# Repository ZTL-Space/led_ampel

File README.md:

# led_ampel
LED-Circui-Board for an old swiss train signal

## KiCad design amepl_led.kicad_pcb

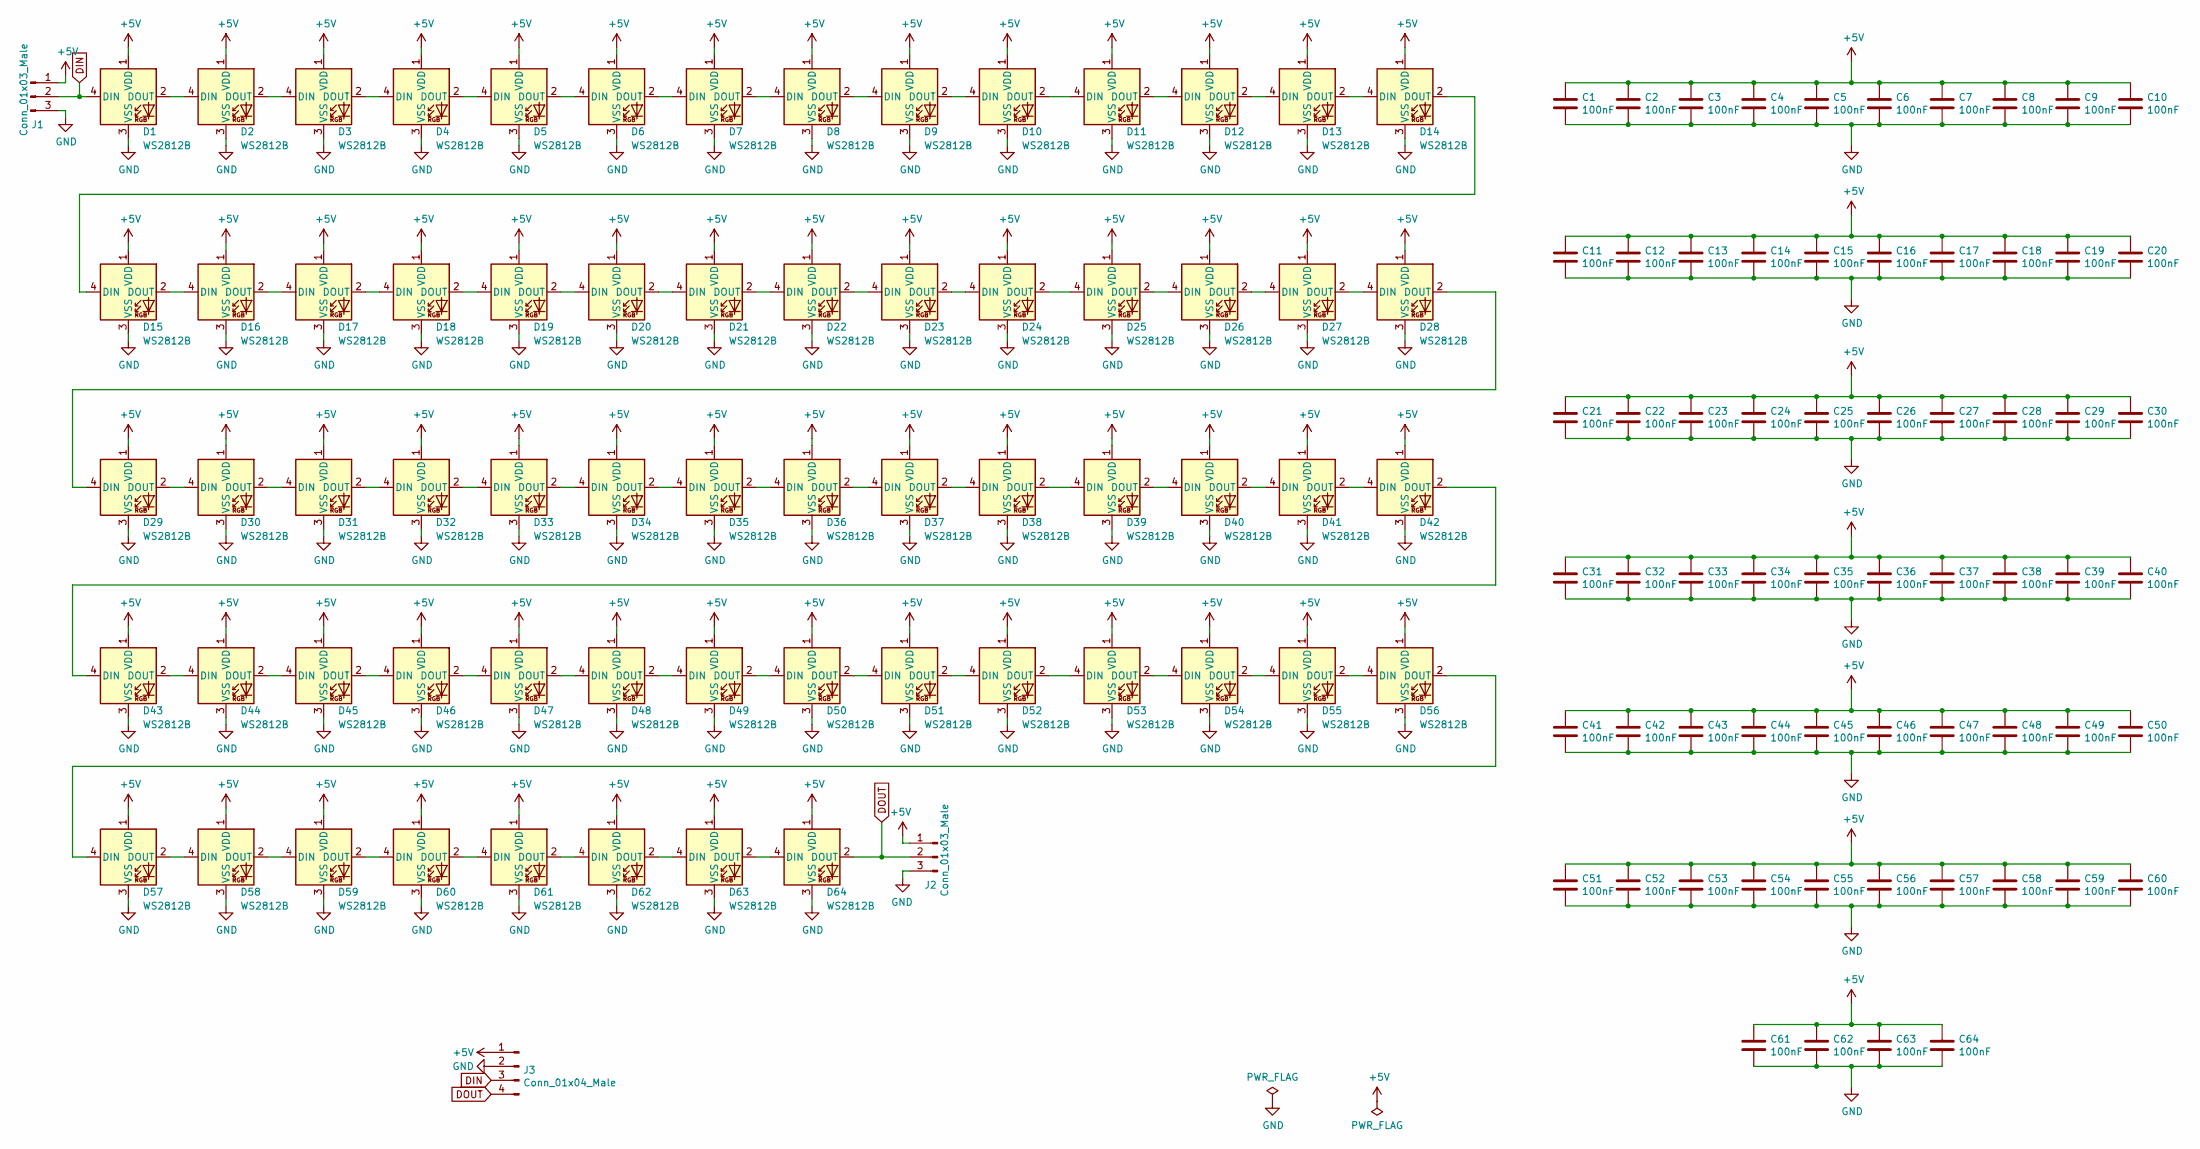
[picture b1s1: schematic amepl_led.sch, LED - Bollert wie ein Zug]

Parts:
C1, C2, C3, C4, C5, C6, C7, C8, C9, C10, C11, C12, C13, C14, C15, C16, C17, C18, C19, C20, C21, C22, C23, C24, C25, C26, C27, C28, C29, C30, C31, C32, C33, C34, C35, C36, C37, C38, C39, C40, C41, C42, C43, C44, C45, C46, C47, C48, C49, C50, C51, C52, C53, C54, C55, C56, C57, C58, C59, C60, C61, C62, C63, C64: 100nF; C_0805_2012Metric_Pad1.18x1.45mm_HandSolder
D1, D2, D3, D4, D5, D6, D7, D8, D9, D10, D11, D12, D13, D14, D15, D16, D17, D18, D19, D20, D21, D22, D23, D24, D25, D26, D27, D28, D29, D30, D31, D32, D33, D34, D35, D36, D37, D38, D39, D40, D41, D42, D43, D44, D45, D46, D47, D48, D49, D50, D51, D52, D53, D54, D55, D56, D57, D58, D59, D60, D61, D62, D63, D64: WS2812B; LED_WS2812B_PLCC4_5.0x5.0mm_P3.2mm
J1, J2: Conn_01x03_Male; JST_XH_B3B-XH-A_1x03_P2.50mm_Vertical
J3: Conn_01x04_Male; PinHeader_1x04_P2.54mm_Vertical

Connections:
+5V: C1.1, C2.1, C3.1, C4.1, C5.1, C6.1, C7.1, C8.1, C9.1, C10.1, C11.1, C12.1, C13.1, C14.1, C15.1, C16.1, C17.1, C18.1, C19.1, C20.1, C21.1, C22.1, C23.1, C24.1, C25.1, C26.1, C27.1, C28.1, C29.1, C30.1, C31.1, C32.1, C33.1, C34.1, C35.1, C36.1, C37.1, C38.1, C39.1, C40.1, C41.1, C42.1, C43.1, C44.1, C45.1, C46.1, C47.1, C48.1, C49.1, C50.1, C51.1, C52.1, C53.1, C54.1, C55.1, C56.1, C57.1, C58.1, C59.1, C60.1, C61.1, C62.1, C63.1, C64.1, D1.1 (VDD), D2.1 (VDD), D3.1 (VDD), D4.1 (VDD), D5.1 (VDD), D6.1 (VDD), D7.1 (VDD), D8.1 (VDD), D9.1 (VDD), D10.1 (VDD), D11.1 (VDD), D12.1 (VDD), D13.1 (VDD), D14.1 (VDD), D15.1 (VDD), D16.1 (VDD), D17.1 (VDD), D18.1 (VDD), D19.1 (VDD), D20.1 (VDD), D21.1 (VDD), D22.1 (VDD), D23.1 (VDD), D24.1 (VDD), D25.1 (VDD), D26.1 (VDD), D27.1 (VDD), D28.1 (VDD), D29.1 (VDD), D30.1 (VDD), D31.1 (VDD), D32.1 (VDD), D33.1 (VDD), D34.1 (VDD), D35.1 (VDD), D36.1 (VDD), D37.1 (VDD), D38.1 (VDD), D39.1 (VDD), D40.1 (VDD), D41.1 (VDD), D42.1 (VDD), D43.1 (VDD), D44.1 (VDD), D45.1 (VDD), D46.1 (VDD), D47.1 (VDD), D48.1 (VDD), D49.1 (VDD), D50.1 (VDD), D51.1 (VDD), D52.1 (VDD), D53.1 (VDD), D54.1 (VDD), D55.1 (VDD), D56.1 (VDD), D57.1 (VDD), D58.1 (VDD), D59.1 (VDD), D60.1 (VDD), D61.1 (VDD), D62.1 (VDD), D63.1 (VDD), D64.1 (VDD), J1.1, J2.1, J3.1
DIN: D1.4 (DIN), J1.2, J3.3
DOUT: D64.2 (DOUT), J2.2, J3.4
GND: C1.2, C2.2, C3.2, C4.2, C5.2, C6.2, C7.2, C8.2, C9.2, C10.2, C11.2, C12.2, C13.2, C14.2, C15.2, C16.2, C17.2, C18.2, C19.2, C20.2, C21.2, C22.2, C23.2, C24.2, C25.2, C26.2, C27.2, C28.2, C29.2, C30.2, C31.2, C32.2, C33.2, C34.2, C35.2, C36.2, C37.2, C38.2, C39.2, C40.2, C41.2, C42.2, C43.2, C44.2, C45.2, C46.2, C47.2, C48.2, C49.2, C50.2, C51.2, C52.2, C53.2, C54.2, C55.2, C56.2, C57.2, C58.2, C59.2, C60.2, C61.2, C62.2, C63.2, C64.2, D1.3 (VSS), D2.3 (VSS), D3.3 (VSS), D4.3 (VSS), D5.3 (VSS), D6.3 (VSS), D7.3 (VSS), D8.3 (VSS), D9.3 (VSS), D10.3 (VSS), D11.3 (VSS), D12.3 (VSS), D13.3 (VSS), D14.3 (VSS), D15.3 (VSS), D16.3 (VSS), D17.3 (VSS), D18.3 (VSS), D19.3 (VSS), D20.3 (VSS), D21.3 (VSS), D22.3 (VSS), D23.3 (VSS), D24.3 (VSS), D25.3 (VSS), D26.3 (VSS), D27.3 (VSS), D28.3 (VSS), D29.3 (VSS), D30.3 (VSS), D31.3 (VSS), D32.3 (VSS), D33.3 (VSS), D34.3 (VSS), D35.3 (VSS), D36.3 (VSS), D37.3 (VSS), D38.3 (VSS), D39.3 (VSS), D40.3 (VSS), D41.3 (VSS), D42.3 (VSS), D43.3 (VSS), D44.3 (VSS), D45.3 (VSS), D46.3 (VSS), D47.3 (VSS), D48.3 (VSS), D49.3 (VSS), D50.3 (VSS), D51.3 (VSS), D52.3 (VSS), D53.3 (VSS), D54.3 (VSS), D55.3 (VSS), D56.3 (VSS), D57.3 (VSS), D58.3 (VSS), D59.3 (VSS), D60.3 (VSS), D61.3 (VSS), D62.3 (VSS), D63.3 (VSS), D64.3 (VSS), J1.3, J2.3, J3.2
unnamed: D1.2 (DOUT), D2.4 (DIN)
unnamed: D2.2 (DOUT), D3.4 (DIN)
unnamed: D3.2 (DOUT), D4.4 (DIN)
unnamed: D4.2 (DOUT), D5.4 (DIN)
unnamed: D5.2 (DOUT), D6.4 (DIN)
unnamed: D6.2 (DOUT), D7.4 (DIN)
unnamed: D7.2 (DOUT), D8.4 (DIN)
unnamed: D8.2 (DOUT), D9.4 (DIN)
unnamed: D10.2 (DOUT), D11.4 (DIN)
unnamed: D9.2 (DOUT), D10.4 (DIN)
unnamed: D11.2 (DOUT), D12.4 (DIN)
unnamed: D12.2 (DOUT), D13.4 (DIN)
unnamed: D13.2 (DOUT), D14.4 (DIN)
unnamed: D14.2 (DOUT), D15.4 (DIN)
unnamed: D15.2 (DOUT), D16.4 (DIN)
unnamed: D16.2 (DOUT), D17.4 (DIN)
unnamed: D17.2 (DOUT), D18.4 (DIN)
unnamed: D18.2 (DOUT), D19.4 (DIN)
unnamed: D19.2 (DOUT), D20.4 (DIN)
unnamed: D20.2 (DOUT), D21.4 (DIN)
unnamed: D21.2 (DOUT), D22.4 (DIN)
unnamed: D22.2 (DOUT), D23.4 (DIN)
unnamed: D23.2 (DOUT), D24.4 (DIN)
unnamed: D24.2 (DOUT), D25.4 (DIN)
unnamed: D25.2 (DOUT), D26.4 (DIN)
unnamed: D26.2 (DOUT), D27.4 (DIN)
unnamed: D27.2 (DOUT), D28.4 (DIN)
unnamed: D28.2 (DOUT), D29.4 (DIN)
unnamed: D29.2 (DOUT), D30.4 (DIN)
unnamed: D30.2 (DOUT), D31.4 (DIN)
unnamed: D31.2 (DOUT), D32.4 (DIN)
unnamed: D32.2 (DOUT), D33.4 (DIN)
unnamed: D33.2 (DOUT), D34.4 (DIN)
unnamed: D34.2 (DOUT), D35.4 (DIN)
unnamed: D35.2 (DOUT), D36.4 (DIN)
unnamed: D36.2 (DOUT), D37.4 (DIN)
unnamed: D37.2 (DOUT), D38.4 (DIN)
unnamed: D38.2 (DOUT), D39.4 (DIN)
unnamed: D39.2 (DOUT), D40.4 (DIN)
unnamed: D40.2 (DOUT), D41.4 (DIN)
unnamed: D41.2 (DOUT), D42.4 (DIN)
unnamed: D42.2 (DOUT), D43.4 (DIN)
unnamed: D43.2 (DOUT), D44.4 (DIN)
unnamed: D44.2 (DOUT), D45.4 (DIN)
unnamed: D45.2 (DOUT), D46.4 (DIN)
unnamed: D46.2 (DOUT), D47.4 (DIN)
unnamed: D47.2 (DOUT), D48.4 (DIN)
unnamed: D48.2 (DOUT), D49.4 (DIN)
unnamed: D49.2 (DOUT), D50.4 (DIN)
unnamed: D50.2 (DOUT), D51.4 (DIN)
unnamed: D51.2 (DOUT), D52.4 (DIN)
unnamed: D52.2 (DOUT), D53.4 (DIN)
unnamed: D53.2 (DOUT), D54.4 (DIN)
unnamed: D54.2 (DOUT), D55.4 (DIN)
unnamed: D55.2 (DOUT), D56.4 (DIN)
unnamed: D56.2 (DOUT), D57.4 (DIN)
unnamed: D57.2 (DOUT), D58.4 (DIN)
unnamed: D58.2 (DOUT), D59.4 (DIN)
unnamed: D59.2 (DOUT), D60.4 (DIN)
unnamed: D60.2 (DOUT), D61.4 (DIN)
unnamed: D61.2 (DOUT), D62.4 (DIN)
unnamed: D62.2 (DOUT), D63.4 (DIN)
unnamed: D63.2 (DOUT), D64.4 (DIN)

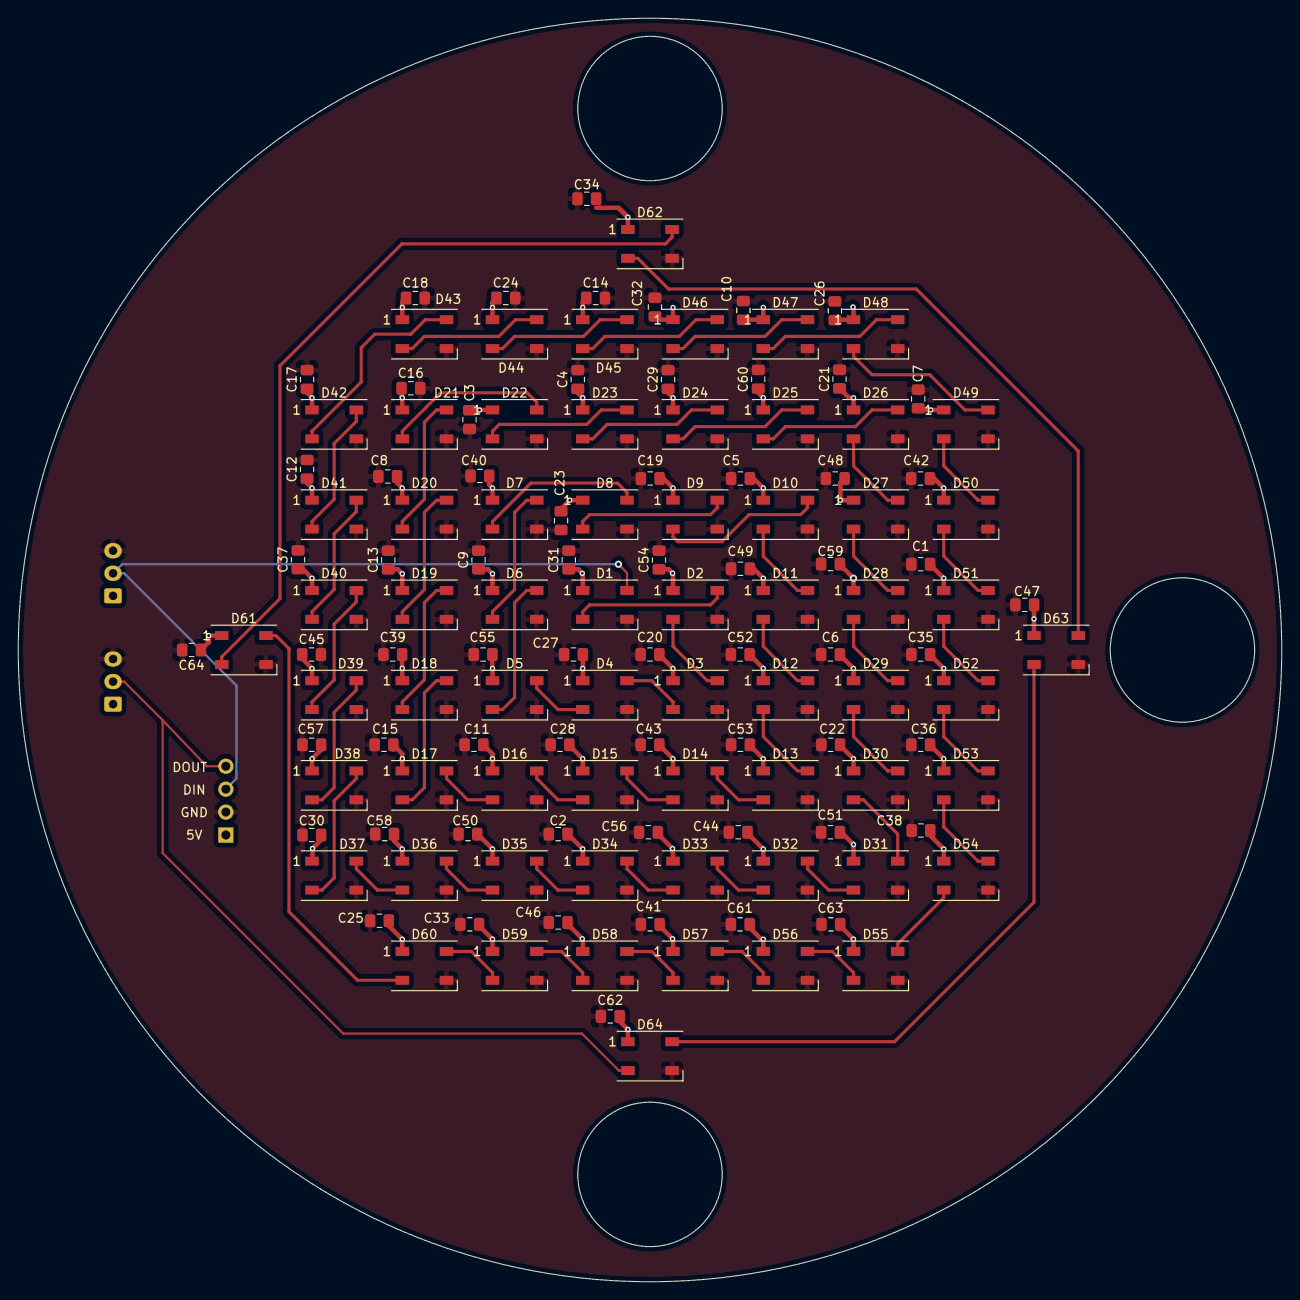
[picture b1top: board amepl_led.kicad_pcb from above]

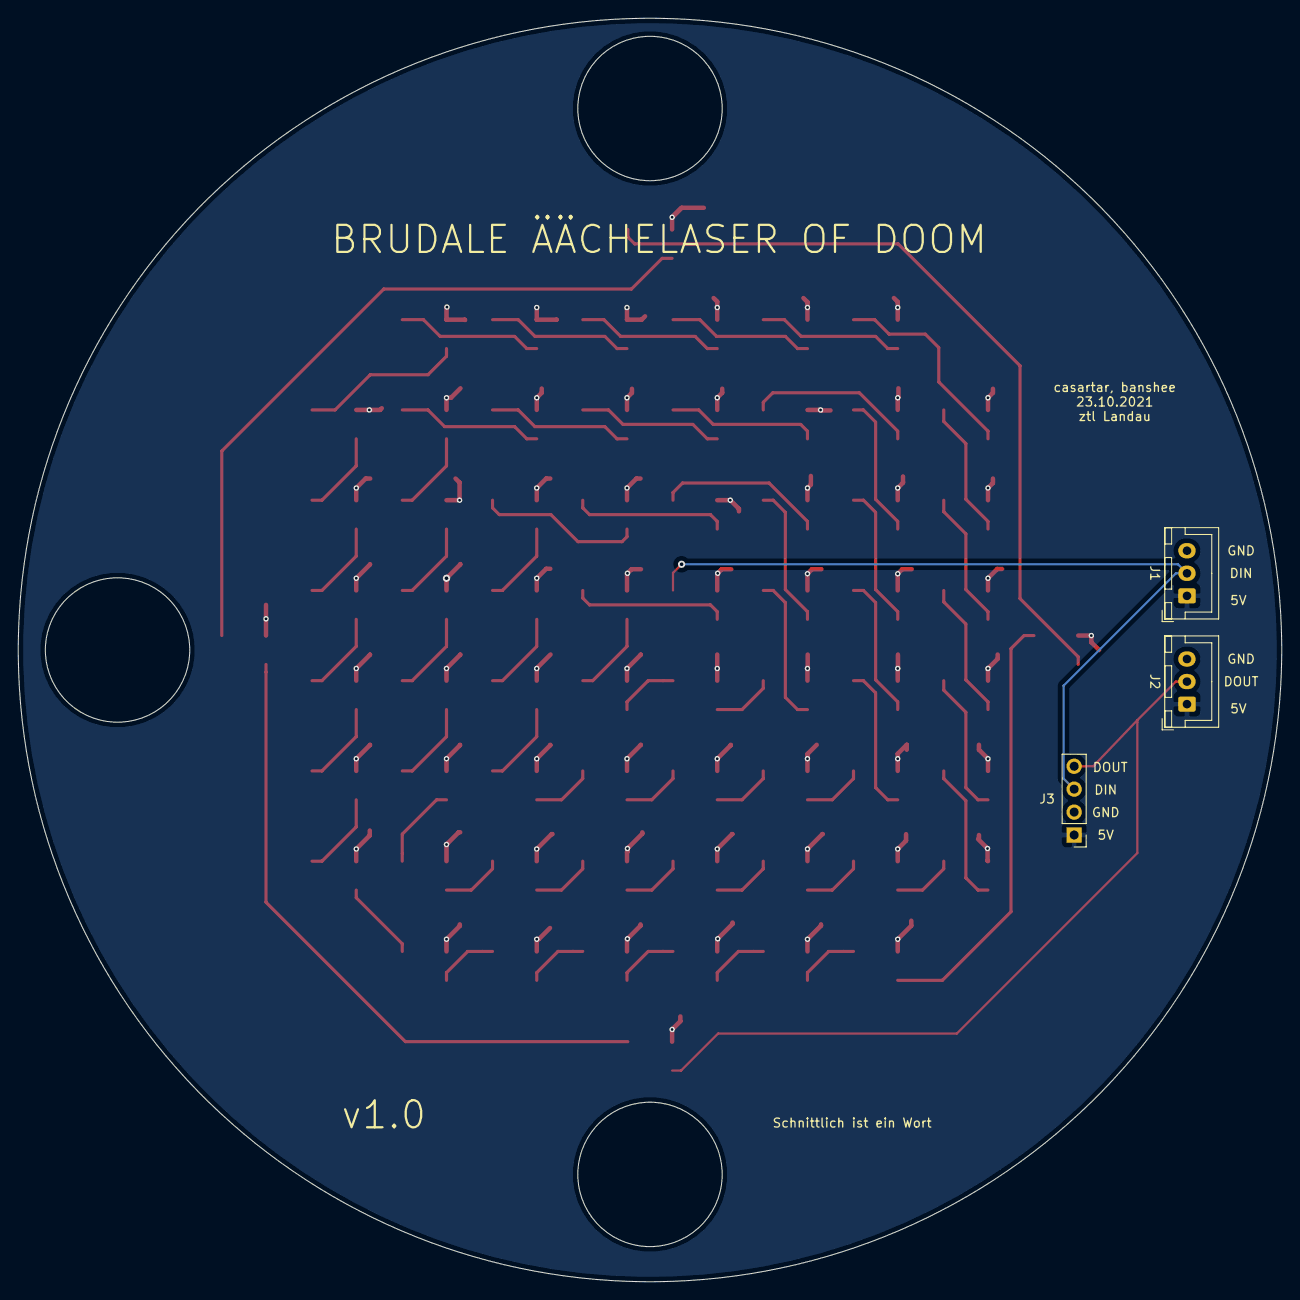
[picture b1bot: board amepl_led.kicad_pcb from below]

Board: 2 copper layers, 140.0 x 140.0 mm, 131 parts (3 on the bottom side), 67 nets.

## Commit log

2021-10-23 initial Commit
    Commit of the full circuit-board.
2021-10-24 Review Korrekturen und Erstellung der Gerber Dateien
2021-10-24 Fertigstellung von v1.0
2021-10-24 Aktualisierung der PDF-Datei
